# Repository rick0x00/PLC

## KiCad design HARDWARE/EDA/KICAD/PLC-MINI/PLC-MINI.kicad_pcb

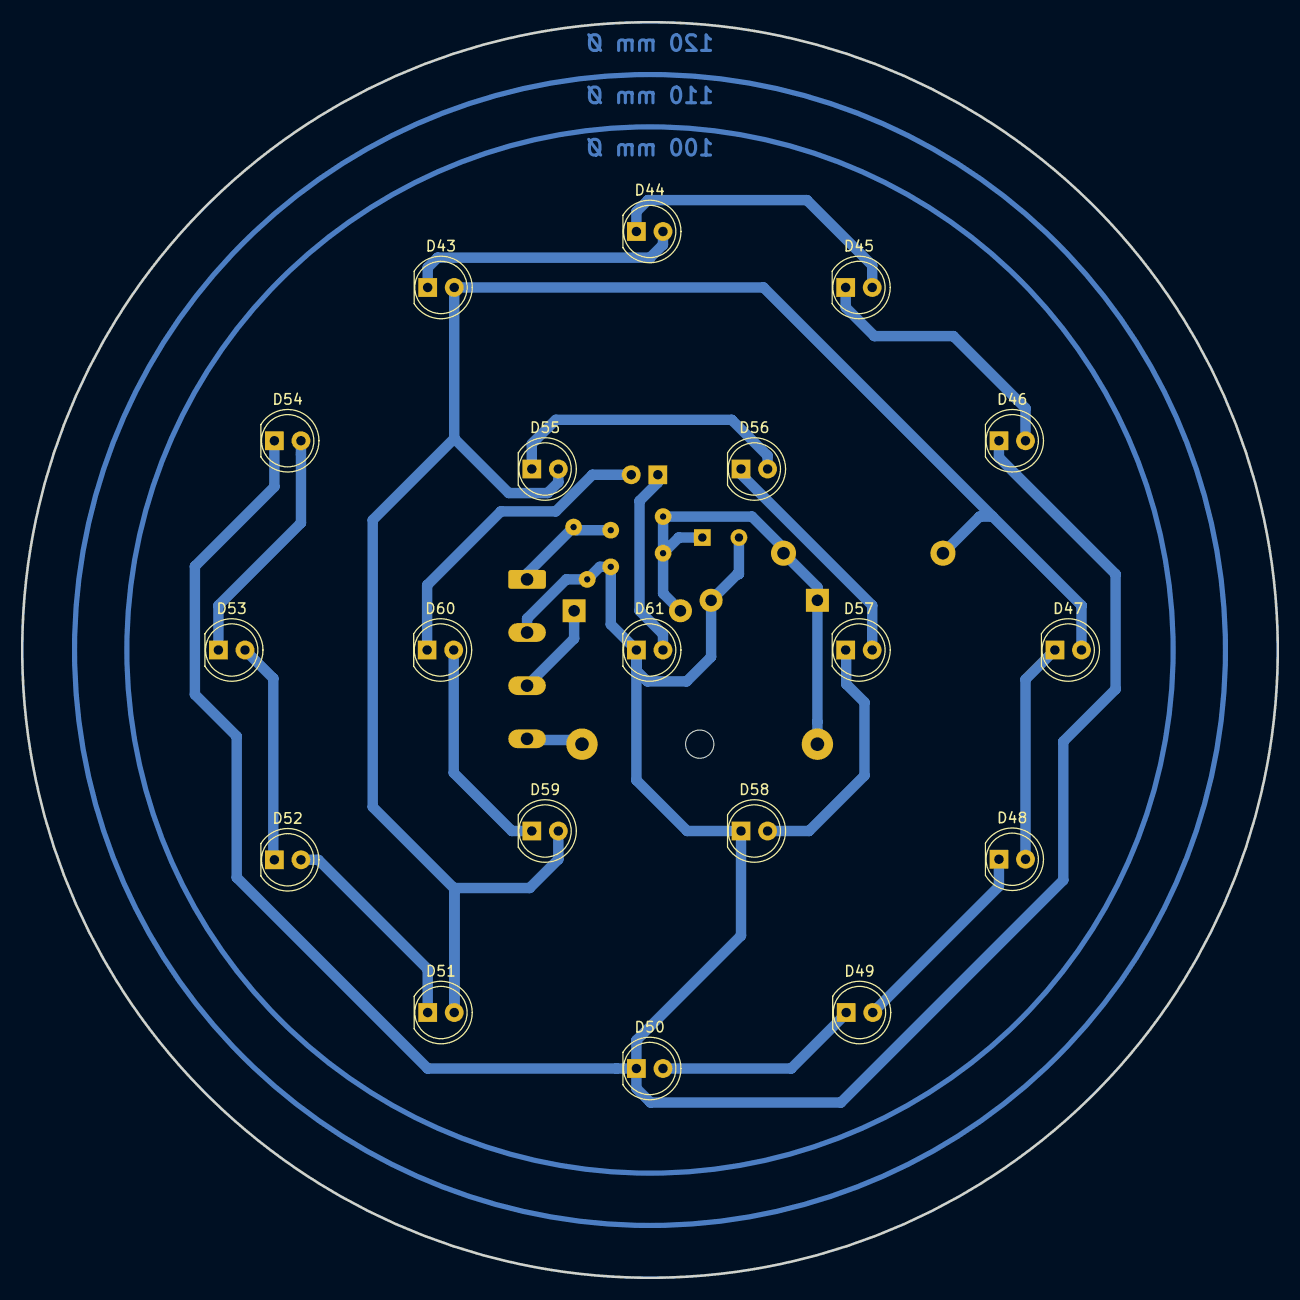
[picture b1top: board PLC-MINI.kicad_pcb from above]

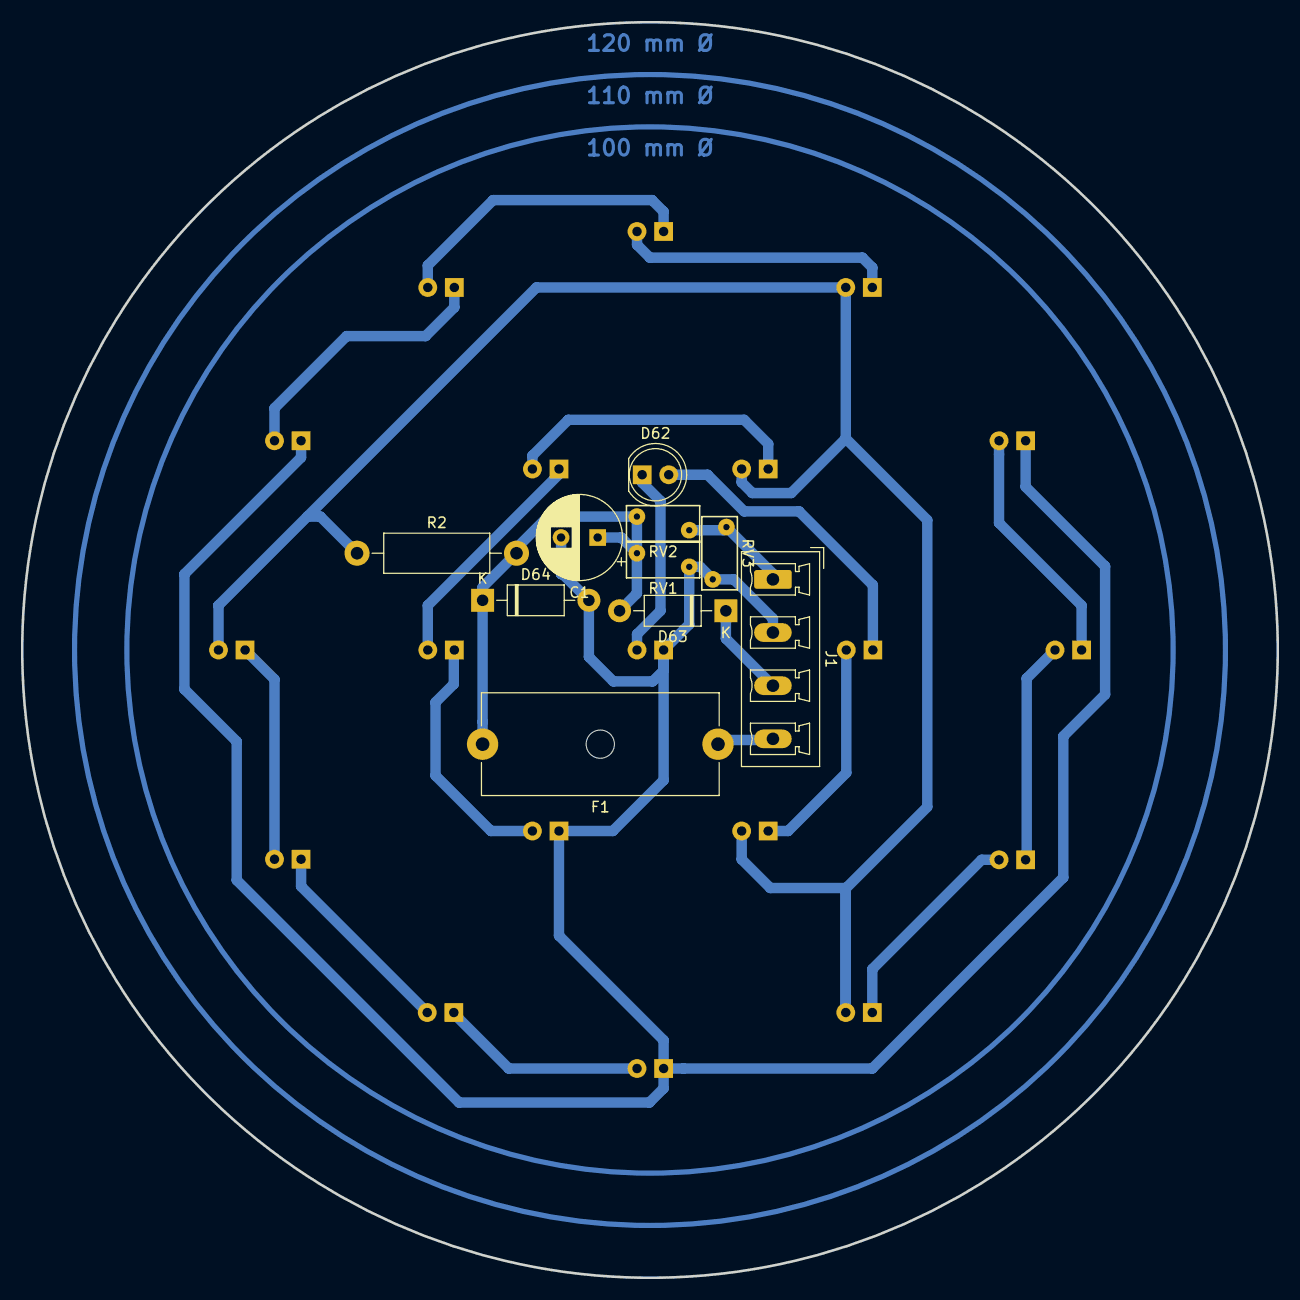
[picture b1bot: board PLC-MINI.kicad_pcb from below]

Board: 2 copper layers, 120.0 x 120.0 mm, 29 parts (10 on the bottom side), 21 nets.

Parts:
C1: 16V 330uf; CP_Radial_D8.0mm_P3.50mm
D43, D44, D45, D46, D59, D60, D61: LED; LED_D5.0mm_IRBlack
D47, D48, D49, D50: LED; LED_D5.0mm_IRGrey
D51, D52, D53, D54: LED; LED_D5.0mm
D55, D56, D57, D58: LED; LED_D5.0mm_Clear
D62: FEEDBACK; LED_D5.0mm_IRBlack
D63: 1N4007; D_DO-41_SOD81_P10.16mm_Horizontal
D64: 1N47xxA; D_DO-41_SOD81_P10.16mm_Horizontal
F1: Fuse 1A; Fuseholder_Cylinder-5x20mm_Schurter_0031_8201_Horizontal_Op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
J1: pw_input; PhoenixContact_MCV_1,5_4-G-5.08_1x04_P5.08mm_Vertical
R2: Rl 2W; R_Axial_DIN0411_L9.9mm_D3.6mm_P15.24mm_Horizontal
RV1, RV2, RV3: 14V; RV_Disc_D7mm_W3.4mm_P5mm

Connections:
Earth: J1.1, RV2.2, RV3.2
GND: C1.2, D46.1, D50.1, D54.1, D58.1, D61.1, D64.2, J1.2, RV1.2, RV3.1
unnamed: C1.1, D63.2, D64.1, F1.2, R2.2, RV1.1, RV2.1
unnamed: D43.1, D44.2
unnamed: D44.1, D45.2
unnamed: D45.1, D46.2
unnamed: D47.1, D48.2
unnamed: D48.1, D49.2
unnamed: D49.1, D50.2
unnamed: D51.1, D52.2
unnamed: D52.1, D53.2
unnamed: D53.1, D54.2
unnamed: D55.1, D56.2
unnamed: D56.1, D57.2
unnamed: D57.1, D58.2
unnamed: D59.1, D60.2
unnamed: D60.1, D62.2
unnamed: D61.2, D62.1
unnamed: D63.1, J1.3
unnamed: F1.1, J1.4
PWR: D43.2, D47.2, D51.2, D55.2, D59.2, R2.1

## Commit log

2021-10-08 add files project kicad
2021-10-08 add circle in PCBNew Kicad
2021-10-08 add LEDS IN ESCHEMA
2021-10-08 Schematic finished
2021-10-08 pause work
2021-10-09 adjusting PCB
2021-10-12 finished project
2021-10-12 update README.md
    add images
2021-10-12 ADD IMAGES
2021-10-12 Adjust IMAGES
2021-10-14 Adjust schematic and PCB
2021-12-02 adjust schematic group 2
2021-12-02 test in pcb
2021-12-02 testes pcb
2021-12-02 project in pcb
2021-12-03 adjust pcb
2021-12-04 reorganized schematic
2021-12-05 finished schematic and PCB
2021-12-05 add files to toggle switch, add new componnents to plc
2021-12-05 finished new schametic
2021-12-07 remix project
2022-04-20 create mini plc
2022-12-29 Add splc
